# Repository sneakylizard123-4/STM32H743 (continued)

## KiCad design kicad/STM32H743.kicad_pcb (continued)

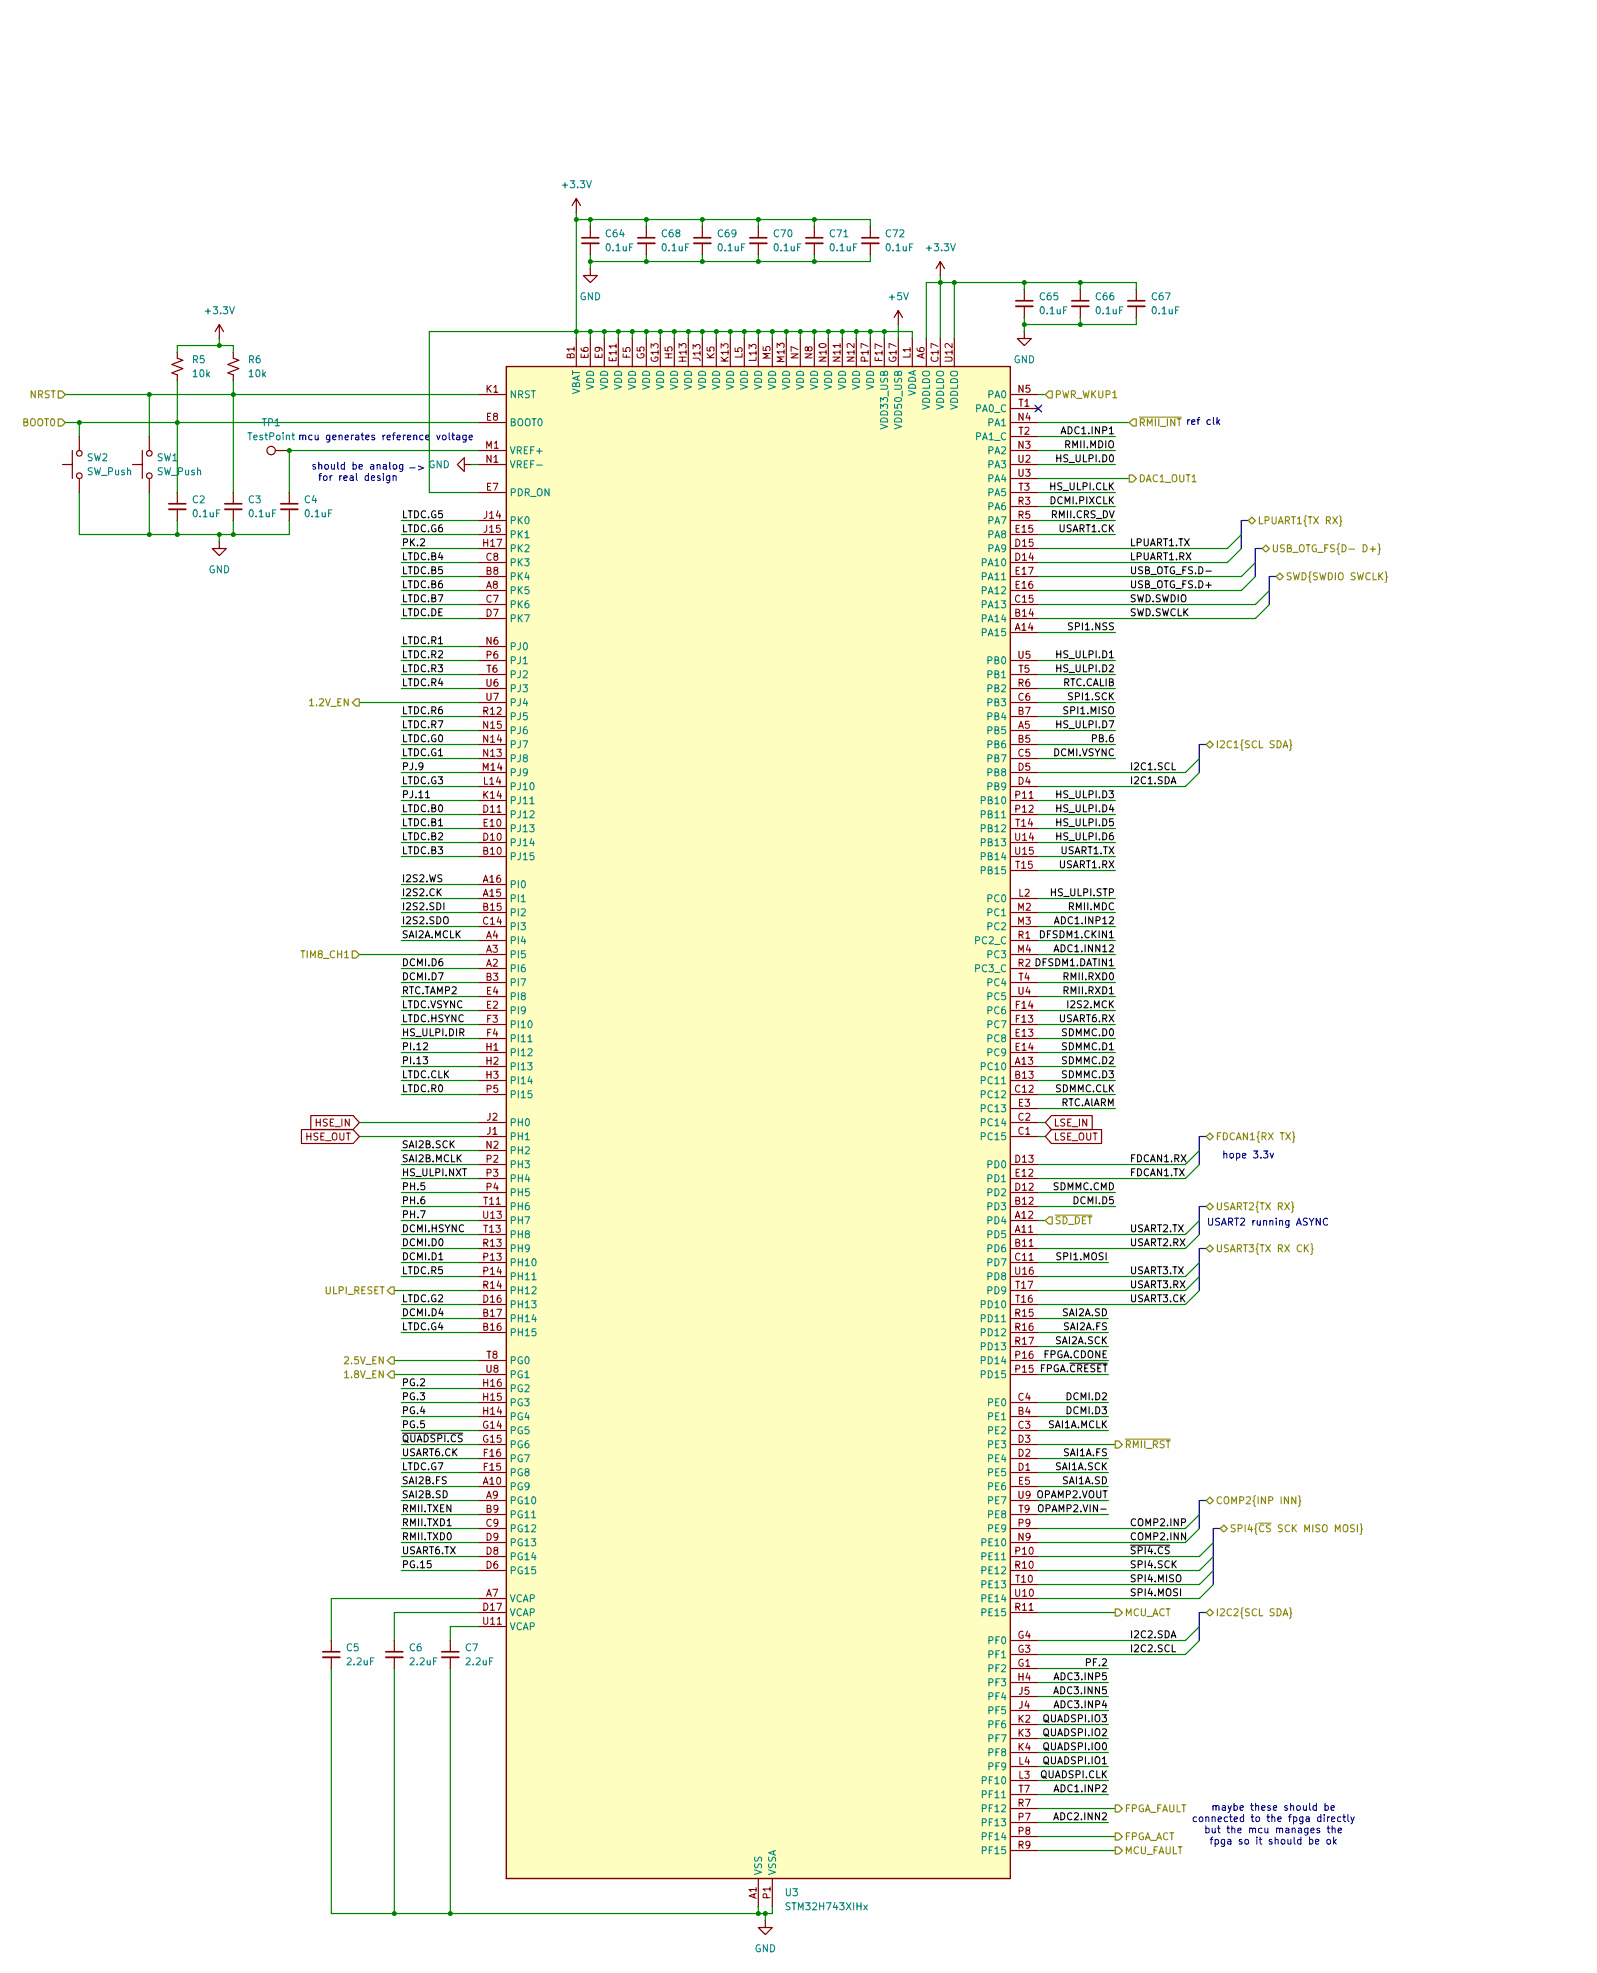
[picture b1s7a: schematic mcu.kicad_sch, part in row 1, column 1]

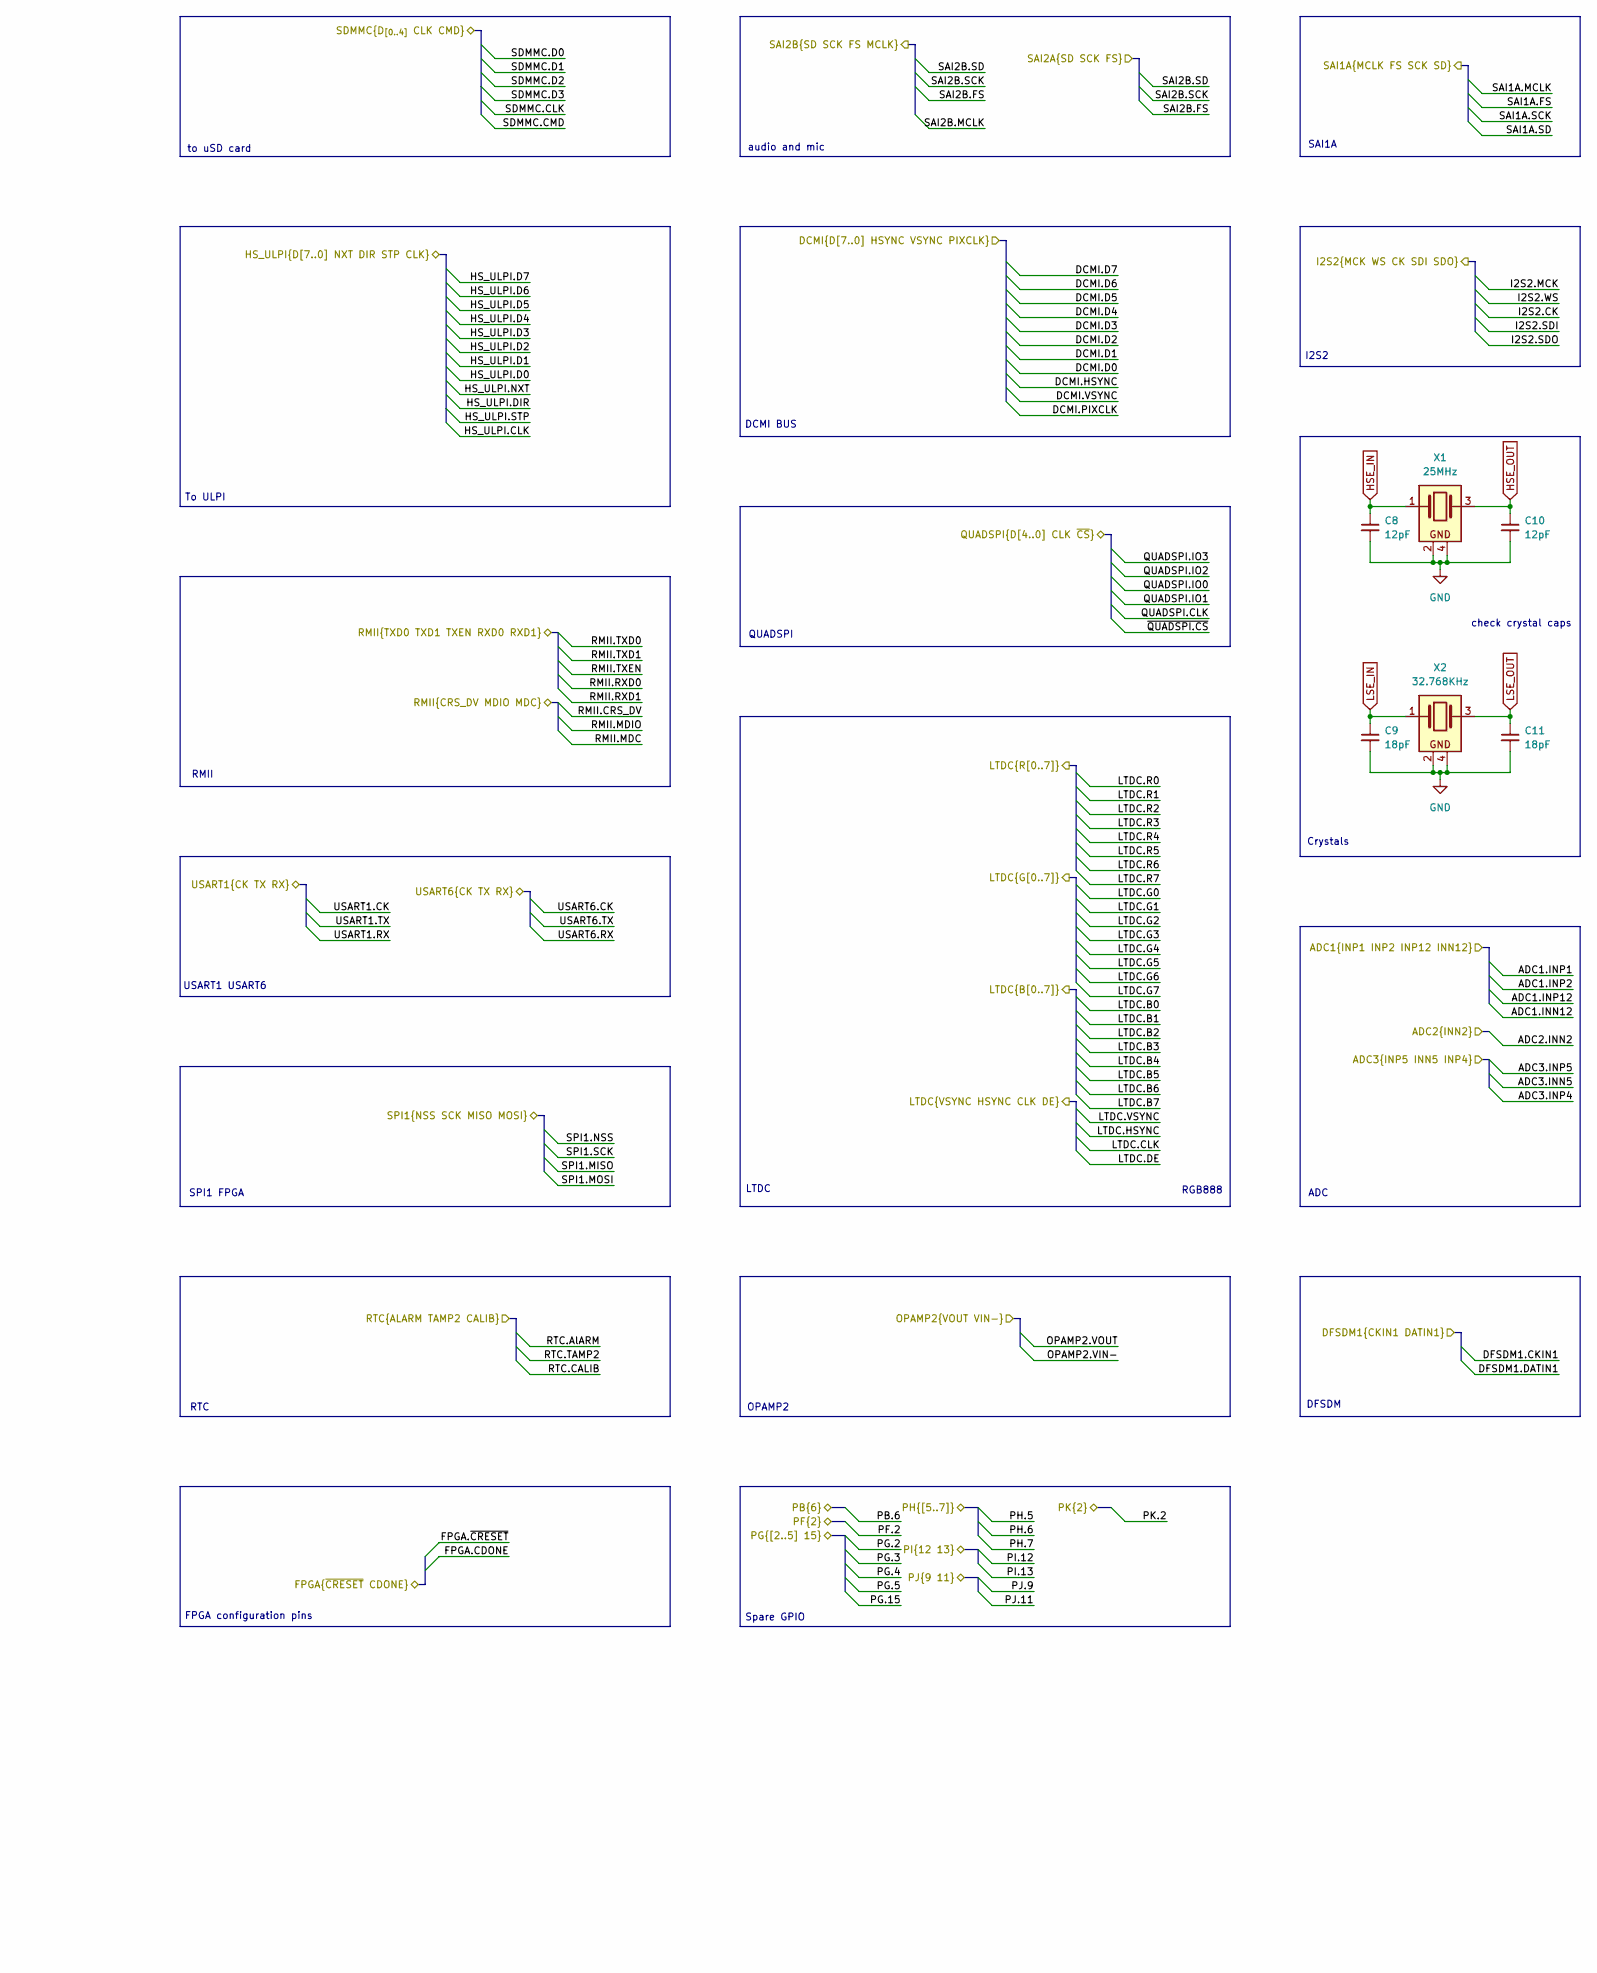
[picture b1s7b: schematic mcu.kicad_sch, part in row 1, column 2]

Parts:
C2, C3, C4, C64, C65, C66, C67, C68, C69, C70, C71, C72: 0.1uF; C_0603_1608Metric
C5, C6, C7: 2.2uF; C_0603_1608Metric
C8, C10: 12pF; C_0603_1608Metric
C9, C11: 18pF; C_0603_1608Metric
R5, R6: 10k; R_0603_1608Metric
SW1, SW2: SW_Push; Panasonic_EVQPUM_EVQPUD
TP1: TestPoint; TestPoint_Pad_D1.5mm
U3: STM32H743XIHx; TFBGA-265_14x14mm_Layout17x17_P0.8mm
X1: 25MHz; Crystal_SMD_3225-4Pin_3.2x2.5mm
X2: 32.768KHz; Crystal_SMD_3225-4Pin_3.2x2.5mm

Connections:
+3.3V: C64.1, C65.1, C66.1, C67.1, C68.1, C69.1, C70.1, C71.1, C72.1, R5.1, R6.1, U3.A6 (VDDLDO), U3.B1 (VBAT), U3.C17 (VDDLDO), U3.E6 (VDD), U3.E7 (PDR_ON), U3.E9 (VDD), U3.E11 (VDD), U3.F5 (VDD), U3.F17 (VDD33_USB), U3.G5 (VDD), U3.G13 (VDD), U3.H5 (VDD), U3.H13 (VDD), U3.J13 (VDD), U3.K5 (VDD), U3.K13 (VDD), U3.L1 (VDDA), U3.L5 (VDD), U3.L13 (VDD), U3.M5 (VDD), U3.M13 (VDD), U3.N7 (VDD), U3.N8 (VDD), U3.N10 (VDD), U3.N11 (VDD), U3.N12 (VDD), U3.P17 (VDD), U3.U12 (VDDLDO); also elsewhere on the board
+5V: U3.G17 (VDD50_USB); also elsewhere on the board
/Audio/DFSDM1.CKIN1: U3.R1 (PC2_C); also elsewhere on the board
/Audio/DFSDM1.DATIN1: U3.R2 (PC3_C); also elsewhere on the board
/Audio/SAI2A.FS: U3.R16 (PD12); also elsewhere on the board
/Audio/SAI2A.SCK: U3.R17 (PD13); also elsewhere on the board
/Audio/SAI2A.SD: U3.R15 (PD11); also elsewhere on the board
/Audio/SAI2B.FS: U3.A10 (PG9); also elsewhere on the board
/Audio/SAI2B.MCLK: U3.P2 (PH3); also elsewhere on the board
/Audio/SAI2B.SCK: U3.N2 (PH2); also elsewhere on the board
/Audio/SAI2B.SD: U3.A9 (PG10); also elsewhere on the board
/Clock/I2C1.SCL: U3.D5 (PB8); also elsewhere on the board
/Clock/I2C1.SDA: U3.D4 (PB9); also elsewhere on the board
/Connector/ADC1.INN12: U3.M4 (PC3)
/Connector/ADC1.INP1: U3.T2 (PA1_C)
/Connector/ADC1.INP2: U3.T7 (PF11)
/Connector/ADC1.INP12: U3.M3 (PC2)
/Connector/ADC2.INN2: U3.P7 (PF13)
/Connector/ADC3.INN5: U3.J5 (PF4)
/Connector/ADC3.INP4: U3.J4 (PF5)
/Connector/ADC3.INP5: U3.H4 (PF3)
/Connector/BOOT0: C2.1, R5.2, SW2.2, U3.E8 (BOOT0)
/Connector/COMP2.INN: U3.N9 (PE10)
/Connector/COMP2.INP: U3.P9 (PE9)
/Connector/DAC1_OUT1: U3.U3 (PA4)
/Connector/DCMI.D0: U3.R13 (PH9)
/Connector/DCMI.D1: U3.P13 (PH10)
/Connector/DCMI.D2: U3.C4 (PE0)
/Connector/DCMI.D3: U3.B4 (PE1)
/Connector/DCMI.D4: U3.B17 (PH14)
/Connector/DCMI.D5: U3.B12 (PD3)
/Connector/DCMI.D6: U3.A2 (PI6)
/Connector/DCMI.D7: U3.B3 (PI7)
/Connector/DCMI.HSYNC: U3.T13 (PH8)
/Connector/DCMI.PIXCLK: U3.R3 (PA6)
/Connector/DCMI.VSYNC: U3.C5 (PB7)
/Connector/FDCAN1.RX: U3.D13 (PD0)
/Connector/FDCAN1.TX: U3.E12 (PD1)
/Connector/I2C2.SCL: U3.G3 (PF1)
/Connector/I2C2.SDA: U3.G4 (PF0)
/Connector/I2S2.CK: U3.A15 (PI1)
/Connector/I2S2.MCK: U3.F14 (PC6)
/Connector/I2S2.SDI: U3.B15 (PI2)
/Connector/I2S2.SDO: U3.C14 (PI3)
/Connector/I2S2.WS: U3.A16 (PI0)
/Connector/LPUART1.RX: U3.D14 (PA10)
/Connector/LPUART1.TX: U3.D15 (PA9)
/Connector/NRST: C3.1, R6.2, SW1.2, U3.K1 (NRST); also elsewhere on the board
/Connector/OPAMP2.VIN-: U3.T9 (PE8)
/Connector/OPAMP2.VOUT: U3.U9 (PE7)
/Connector/PWR_WKUP1: U3.N5 (PA0)
/Connector/QUADSPI.CLK: U3.L3 (PF10)
/Connector/RTC.CALIB: U3.R6 (PB2)
/Connector/RTC.TAMP2: U3.E4 (PI8)
/Connector/SAI1A.FS: U3.D2 (PE4)
/Connector/SAI1A.MCLK: U3.C3 (PE2)
/Connector/SAI1A.SCK: U3.D1 (PE5)
/Connector/SAI1A.SD: U3.E5 (PE6)
/Connector/SPI4.MISO: U3.T10 (PE13)
/Connector/SPI4.MOSI: U3.U10 (PE14)
/Connector/SPI4.SCK: U3.R10 (PE12)
/Connector/TIM8_CH1: U3.A3 (PI5)
/Connector/USART1.CK: U3.E15 (PA8)
/Connector/USART1.RX: U3.T15 (PB15)
/Connector/USART1.TX: U3.U15 (PB14)
/Connector/USART2.RX: U3.B11 (PD6)
/Connector/USART2.TX: U3.A11 (PD5)
/Connector/USART3.CK: U3.T16 (PD10)
/Connector/USART3.RX: U3.T17 (PD9)
/Connector/USART3.TX: U3.U16 (PD8)
/Connector/USART6.CK: U3.F16 (PG7)
/Connector/USART6.RX: U3.F13 (PC7)
/Connector/USART6.TX: U3.D8 (PG14)
/Ethernet/RMII.CRS_DV: U3.R5 (PA7); also elsewhere on the board
/Ethernet/RMII.MDC: U3.M2 (PC1); also elsewhere on the board
/Ethernet/RMII.MDIO: U3.N3 (PA2); also elsewhere on the board
/Ethernet/RMII.RXD0: U3.T4 (PC4); also elsewhere on the board
/Ethernet/RMII.RXD1: U3.U4 (PC5); also elsewhere on the board
/Ethernet/RMII.TXD0: U3.D9 (PG13); also elsewhere on the board
/Ethernet/RMII.TXD1: U3.C9 (PG12); also elsewhere on the board
/Ethernet/RMII.TXEN: U3.B9 (PG11); also elsewhere on the board
/Ethernet/~RMII_INT: U3.N4 (PA1); also elsewhere on the board
/Ethernet/~RMII_RST: U3.D3 (PE3); also elsewhere on the board
/FPGA/FPGA.CDONE: U3.P16 (PD14); also elsewhere on the board
/FPGA/FPGA.~CRESET: U3.P15 (PD15); also elsewhere on the board
/FPGA/SPI1.MISO: U3.B7 (PB4); also elsewhere on the board
/FPGA/SPI1.MOSI: U3.C11 (PD7); also elsewhere on the board
/FPGA/SPI1.NSS: U3.A14 (PA15); also elsewhere on the board
/FPGA/SPI1.SCK: U3.C6 (PB3); also elsewhere on the board
/GPIO/PB.6: U3.B5 (PB6); also elsewhere on the board
/GPIO/PF.2: U3.G1 (PF2); also elsewhere on the board
/GPIO/PG.2: U3.H16 (PG2); also elsewhere on the board
/GPIO/PG.3: U3.H15 (PG3); also elsewhere on the board
/GPIO/PG.4: U3.H14 (PG4); also elsewhere on the board
/GPIO/PG.5: U3.G14 (PG5); also elsewhere on the board
/GPIO/PG.15: U3.D6 (PG15); also elsewhere on the board
/GPIO/PH.5: U3.P4 (PH5); also elsewhere on the board
/GPIO/PH.6: U3.T11 (PH6); also elsewhere on the board
/GPIO/PH.7: U3.U13 (PH7); also elsewhere on the board
/GPIO/PI.12: U3.H1 (PI12); also elsewhere on the board
/GPIO/PI.13: U3.H2 (PI13); also elsewhere on the board
/GPIO/PJ.9: U3.M14 (PJ9); also elsewhere on the board
/GPIO/PJ.11: U3.K14 (PJ11); also elsewhere on the board
/GPIO/PK.2: U3.H17 (PK2); also elsewhere on the board
/LEDs/FPGA_ACT: U3.P8 (PF14); also elsewhere on the board
/LEDs/FPGA_FAULT: U3.R7 (PF12); also elsewhere on the board
/LEDs/MCU_ACT: U3.R11 (PE15); also elsewhere on the board
/LEDs/MCU_FAULT: U3.R9 (PF15); also elsewhere on the board
/LTDC/LTDC.B0: U3.D11 (PJ12)
/LTDC/LTDC.B1: U3.E10 (PJ13)
/LTDC/LTDC.B2: U3.D10 (PJ14)
/LTDC/LTDC.B3: U3.B10 (PJ15)
/LTDC/LTDC.B4: U3.C8 (PK3)
/LTDC/LTDC.B5: U3.B8 (PK4)
/LTDC/LTDC.B6: U3.A8 (PK5)
/LTDC/LTDC.B7: U3.C7 (PK6)
/LTDC/LTDC.CLK: U3.H3 (PI14)
/LTDC/LTDC.DE: U3.D7 (PK7)
/LTDC/LTDC.G0: U3.N14 (PJ7)
/LTDC/LTDC.G1: U3.N13 (PJ8)
/LTDC/LTDC.G2: U3.D16 (PH13)
/LTDC/LTDC.G3: U3.L14 (PJ10)
/LTDC/LTDC.G4: U3.B16 (PH15)
/LTDC/LTDC.G5: U3.J14 (PK0)
/LTDC/LTDC.G6: U3.J15 (PK1)
/LTDC/LTDC.G7: U3.F15 (PG8)
/LTDC/LTDC.HSYNC: U3.F3 (PI10)
/LTDC/LTDC.R0: U3.P5 (PI15)
/LTDC/LTDC.R1: U3.N6 (PJ0)
/LTDC/LTDC.R2: U3.P6 (PJ1)
/LTDC/LTDC.R3: U3.T6 (PJ2)
/LTDC/LTDC.R4: U3.U6 (PJ3)
/LTDC/LTDC.R5: U3.P14 (PH11)
/LTDC/LTDC.R6: U3.R12 (PJ5)
/LTDC/LTDC.R7: U3.N15 (PJ6)
/LTDC/LTDC.VSYNC: U3.E2 (PI9)
/MCU/1.2V_EN: U3.U7 (PJ4); also elsewhere on the board
/MCU/1.8V_EN: U3.U8 (PG1); also elsewhere on the board
/MCU/2.5V_EN: U3.T8 (PG0); also elsewhere on the board
/MCU/HS_ULPI.CLK: U3.T3 (PA5); also elsewhere on the board
/MCU/HS_ULPI.D0: U3.U2 (PA3); also elsewhere on the board
/MCU/HS_ULPI.D1: U3.U5 (PB0); also elsewhere on the board
/MCU/HS_ULPI.D2: U3.T5 (PB1); also elsewhere on the board
/MCU/HS_ULPI.D3: U3.P11 (PB10); also elsewhere on the board
/MCU/HS_ULPI.D4: U3.P12 (PB11); also elsewhere on the board
/MCU/HS_ULPI.D5: U3.T14 (PB12); also elsewhere on the board
/MCU/HS_ULPI.D6: U3.U14 (PB13); also elsewhere on the board
/MCU/HS_ULPI.D7: U3.A5 (PB5); also elsewhere on the board
/MCU/HS_ULPI.DIR: U3.F4 (PI11); also elsewhere on the board
/MCU/HS_ULPI.NXT: U3.P3 (PH4); also elsewhere on the board
/MCU/HS_ULPI.STP: U3.L2 (PC0); also elsewhere on the board
/MCU/QUADSPI.IO0: U3.K4 (PF8)
/MCU/QUADSPI.IO1: U3.L4 (PF9)
/MCU/QUADSPI.IO2: U3.K3 (PF7)
/MCU/QUADSPI.IO3: U3.K2 (PF6)
/MCU/RTC.AlARM: U3.E3 (PC13)
/MCU/SAI2A.MCLK: U3.A4 (PI4)
/MCU/USB_OTG_FS.D+: U3.E16 (PA12); also elsewhere on the board
/MCU/USB_OTG_FS.D-: U3.E17 (PA11); also elsewhere on the board
/MCU/~QUADSPI.CS: U3.G15 (PG6)
/MCU/~SD_DET: U3.A12 (PD4); also elsewhere on the board
/MCU/~SPI4.CS: U3.P10 (PE11)
GND: C2.2, C3.2, C4.2, C5.2, C6.2, C7.2, C8.2, C9.2, C10.2, C11.2, C64.2, C65.2, C66.2, C67.2, C68.2, C69.2, C70.2, C71.2, C72.2, SW1.1, SW2.1, U3.A1 (VSS), U3.A17 (VSS), U3.B2 (VSS), U3.B6 (VSS), U3.C10 (VSS), U3.C13 (VSS), U3.C16 (VSS), U3.F1 (VSS), U3.F2 (VSS), U3.G2 (VSS), U3.G7 (VSS), U3.G8 (VSS), U3.G9 (VSS), U3.G10 (VSS), U3.G11 (VSS), U3.G16 (VSS), U3.H7 (VSS), U3.H8 (VSS), U3.H9 (VSS), U3.H10 (VSS), U3.H11 (VSS), U3.J3 (VSS), U3.J7 (VSS), U3.J8 (VSS), U3.J9 (VSS), U3.J10 (VSS), U3.J11 (VSS), U3.J16 (VSS), U3.J17 (VSS), U3.K7 (VSS), U3.K8 (VSS), U3.K9 (VSS), U3.K10 (VSS), U3.K11 (VSS), U3.K15 (VSS), U3.L7 (VSS), U3.L8 (VSS), U3.L9 (VSS), U3.L10 (VSS), U3.L11 (VSS), U3.L15 (VSS), U3.M15 (VSS), U3.N1 (VREF-), U3.N16 (VSS), U3.P1 (VSSA), U3.R4 (VSS), U3.R8 (VSS), U3.T12 (VSS), U3.U1 (VSS), U3.U17 (VSS), X1.2, X1.4, X2.2, X2.4; also elsewhere on the board
HSE_IN: C8.1, U3.J2 (PH0), X1.1
HSE_OUT: C10.1, U3.J1 (PH1), X1.3
LSE_IN: C9.1, U3.C2 (PC14), X2.1
LSE_OUT: C11.1, U3.C1 (PC15), X2.3
unnamed: C5.1, U3.A7 (VCAP)
unnamed: C6.1, U3.D17 (VCAP)
unnamed: C7.1, U3.U11 (VCAP)
unnamed: C4.1, TP1.1 (1_1), U3.M1 (VREF+)
SD_CLK: U3.C12; also elsewhere on the board
SD_CMD: U3.D12 (PD2); also elsewhere on the board
SD_DAT0: U3.E13 (PC8); also elsewhere on the board
SD_DAT1: U3.E14 (PC9); also elsewhere on the board
SD_DAT2: U3.A13 (PC10); also elsewhere on the board
SD_DAT3: U3.B13 (PC11); also elsewhere on the board
SWCLK: U3.B14 (PA14); also elsewhere on the board
SWDIO: U3.C15 (PA13); also elsewhere on the board
~ULPI_RESET: U3.R14 (PH12); also elsewhere on the board

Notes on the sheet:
RGB888
SAI1A
USART2 running ASYNC
mcu generates reference voltage
Spare GPIO
OPAMP2
I2S2
To ULPI
audio and mic
ADC
DCMI BUS
maybe these should be connected to the fpga directly but the mcu manages the fpga so it should be ok
check crystal caps
RMII
SPI1 FPGA
LTDC
to uSD card
FPGA configuration pins
USART1 USART6
QUADSPI
RTC
should be analog for real design
hope 3.3v
ref clk
DFSDM
Crystals

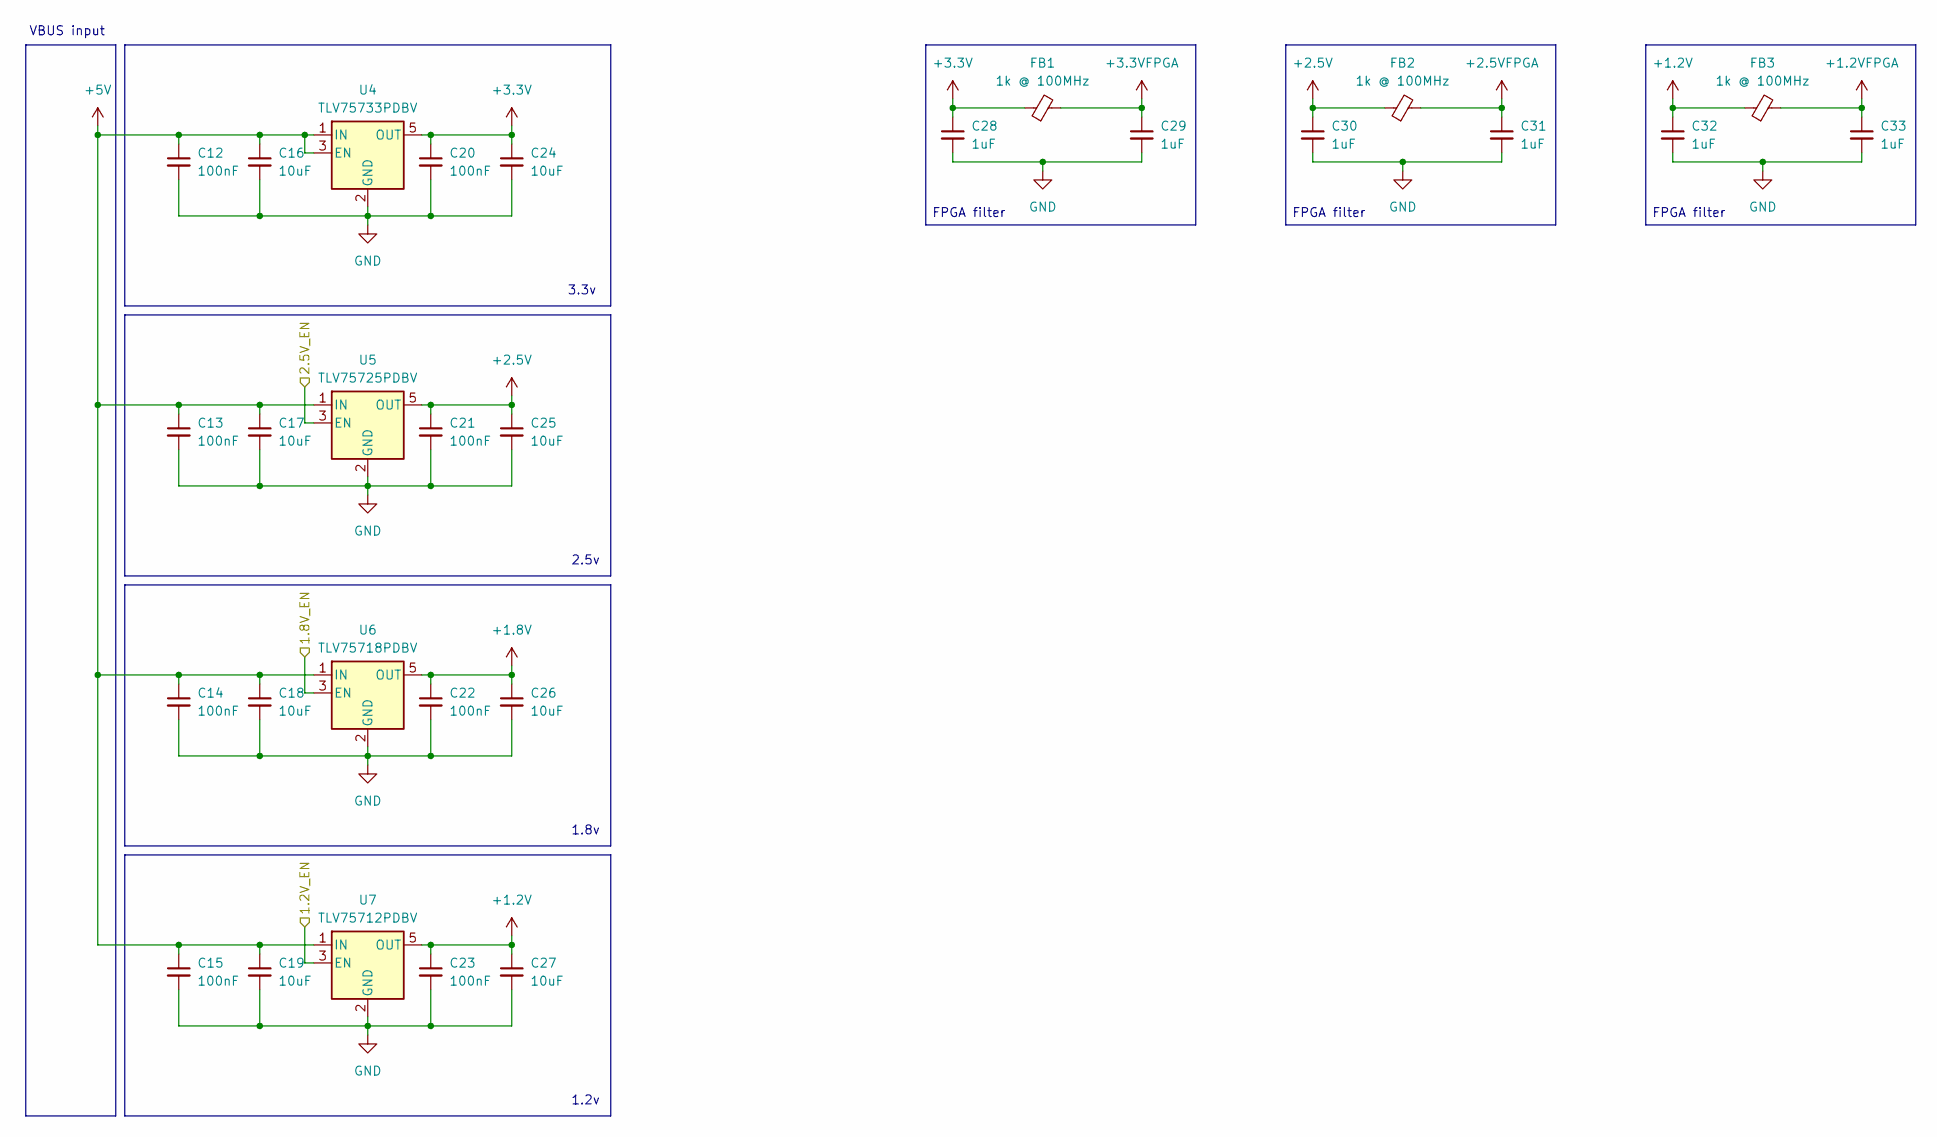
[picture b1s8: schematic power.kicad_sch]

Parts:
C12, C13, C14, C15, C20, C21, C22, C23: 100nF; C_0603_1608Metric
C16, C17, C18, C19, C24, C25, C26, C27: 10uF; C_0603_1608Metric
C28, C29, C30, C31, C32, C33: 1uF; C_0603_1608Metric
FB1, FB2, FB3: 1k @ 100MHz; Ferrite_0603_1608Metric
U4: TLV75733PDBV; SOT-23-5
U5: TLV75725PDBV; SOT-23-5
U6: TLV75718PDBV; SOT-23-5
U7: TLV75712PDBV; SOT-23-5

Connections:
+1.2V: C23.1, C27.1, C32.1, FB3.1, U7.5 (OUT); also elsewhere on the board
+1.2VFPGA: C33.1, FB3.2; also elsewhere on the board
+1.8V: C22.1, C26.1, U6.5 (OUT); also elsewhere on the board
+2.5V: C21.1, C25.1, C30.1, FB2.1, U5.5 (OUT); also elsewhere on the board
+2.5VFPGA: C31.1, FB2.2; also elsewhere on the board
+3.3V: C20.1, C24.1, C28.1, FB1.1, U4.5 (OUT); also elsewhere on the board
+3.3VFPGA: C29.1, FB1.2; also elsewhere on the board
+5V: C12.1, C13.1, C14.1, C15.1, C16.1, C17.1, C18.1, C19.1, U4.1 (IN), U4.3 (EN), U5.1 (IN), U6.1 (IN), U7.1 (IN); also elsewhere on the board
/MCU/1.2V_EN: U7.3 (EN); also elsewhere on the board
/MCU/1.8V_EN: U6.3 (EN); also elsewhere on the board
/MCU/2.5V_EN: U5.3 (EN); also elsewhere on the board
GND: C12.2, C13.2, C14.2, C15.2, C16.2, C17.2, C18.2, C19.2, C20.2, C21.2, C22.2, C23.2, C24.2, C25.2, C26.2, C27.2, C28.2, C29.2, C30.2, C31.2, C32.2, C33.2, U4.2 (GND), U5.2 (GND), U6.2 (GND), U7.2 (GND); also elsewhere on the board

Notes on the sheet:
1.8v
VBUS input
3.3v
FPGA filter
2.5v
1.2v

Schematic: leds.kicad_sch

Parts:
D3, D4, D5, D6: GREEN; LED_0603_1608Metric
D7, D9: YELLOW; LED_0603_1608Metric
D8, D10: RED; LED_0603_1608Metric
RN1, RN2: 1k; R_Array_Concave_4x0603

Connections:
+1.2V: RN1.1 (R1.1); also elsewhere on the board
+1.8V: RN1.2 (R2.1); also elsewhere on the board
+2.5V: RN1.3 (R3.1); also elsewhere on the board
+3.3V: RN1.4 (R4.1); also elsewhere on the board
/LEDs/FPGA_ACT: RN2.2 (R2.1); also elsewhere on the board
/LEDs/FPGA_FAULT: RN2.1 (R1.1); also elsewhere on the board
/LEDs/MCU_ACT: RN2.4 (R4.1); also elsewhere on the board
/LEDs/MCU_FAULT: RN2.3 (R3.1); also elsewhere on the board
GND: D3.1 (K), D4.1 (K), D5.1 (K), D6.1 (K), D7.1 (K), D8.1 (K), D9.1 (K), D10.1 (K); also elsewhere on the board
unnamed: D3.2 (A), RN1.5 (R4.2)
unnamed: D4.2 (A), RN1.6 (R3.2)
unnamed: D5.2 (A), RN1.7 (R2.2)
unnamed: D6.2 (A), RN1.8 (R1.2)
unnamed: D7.2 (A), RN2.5 (R4.2)
unnamed: D8.2 (A), RN2.6 (R3.2)
unnamed: D9.2 (A), RN2.7 (R2.2)
unnamed: D10.2 (A), RN2.8 (R1.2)

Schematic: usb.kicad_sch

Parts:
C1: 120uF; C_0603_1608Metric
D1, D2: SMF12A; D_SMF
J1: USB_A; USB_A_Connfly_DS1095
J2: USB_C_Receptacle_USB2.0_16P; USB_C_Receptacle_HRO_TYPE-C-31-M-12
R1, R2: 22; R_0603_1608Metric
R3, R4: 5.1k; R_0603_1608Metric
U1, U2: USBLC6-2SC6; SOT-23-6

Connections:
+5V: D2.1 (A1), J2.A4 (VBUS), J2.A9 (VBUS), J2.B4 (VBUS), J2.B9 (VBUS), U2.5 (VBUS); also elsewhere on the board
/MCU/USB_OTG_FS.D+: R2.2; also elsewhere on the board
/MCU/USB_OTG_FS.D-: R1.2; also elsewhere on the board
/ULPI/USBA.D+: U1.4 (I/O2); also elsewhere on the board
/ULPI/USBA.D-: U1.6 (I/O1); also elsewhere on the board
/ULPI/USBA.VBUS: C1.1, D1.1 (A1), J1.1 (VBUS), U1.5 (VBUS); also elsewhere on the board
GND: C1.2, D1.2 (A2), D2.2 (A2), J1.4 (GND), J1.SH (Shield), J2.A1 (GND), J2.A12 (GND), J2.B1 (GND), J2.B12 (GND), J2.SH (SHIELD), R3.2, R4.2, U1.2 (GND), U2.2 (GND); also elsewhere on the board
unnamed: J1.3 (D+), U1.1 (I/O1)
unnamed: J1.2 (D-), U1.3 (I/O2)
unnamed: J2.A5 (CC1), R4.1
unnamed: J2.B5 (CC2), R3.1
unnamed: J2.A6 (D+), J2.B6 (D+), U2.3 (I/O2)
unnamed: J2.A7 (D-), J2.B7 (D-), U2.1 (I/O1)
unnamed: R1.1, U2.6 (I/O1)
unnamed: R2.1, U2.4 (I/O2)

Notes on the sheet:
anti zap
USB port
12v tvs
might run shield though capacitor later
USB Host
ringing prevention

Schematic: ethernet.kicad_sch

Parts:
C34: 1uF; C_0603_1608Metric
C35: 470pF; C_0603_1608Metric
C36: 22nF 50v; C_0603_1608Metric
C92, C93, C94, C95, C96: 0.1uF; C_0603_1608Metric
J3: RJ45_Halo_HFJ11-x2450E-LxxRL; RJ45_HALO_HFJ11-x2450E-LxxRL_Horizontal
R7, R8: 10k; R_0603_1608Metric
R9: 12.1k 1%; R_0603_1608Metric
R10, R11: 330; R_0603_1608Metric
U8: LAN8742A; VQFN-24-1EP_4x4mm_P0.5mm_EP2.5x2.5mm_ThermalVias

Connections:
+3.3V: C92.1, C93.1, C94.1, C95.1, C96.1, J3.9, J3.11, R7.1, R8.1, U8.1 (VDD2A), U8.9 (VDDIO), U8.19 (VDD1A); also elsewhere on the board
/Clock/ETH_CLK: U8.5 (XTAL1/CLKIN); also elsewhere on the board
/Ethernet/RD+: J3.3 (RD+), U8.23 (RXP)
/Ethernet/RD-: J3.6 (RD-), U8.22 (RXN)
/Ethernet/RMII.CRS_DV: U8.11 (CRS_DV/MODE2); also elsewhere on the board
/Ethernet/RMII.MDC: U8.13 (MDC); also elsewhere on the board
/Ethernet/RMII.MDIO: U8.12 (MDIO); also elsewhere on the board
/Ethernet/RMII.RXD0: U8.8 (RXD0/MODE0); also elsewhere on the board
/Ethernet/RMII.RXD1: U8.7 (RXD1/MODE1); also elsewhere on the board
/Ethernet/RMII.TXD0: U8.17 (TXD0); also elsewhere on the board
/Ethernet/RMII.TXD1: U8.18 (TXD1); also elsewhere on the board
/Ethernet/RMII.TXEN: U8.16 (TXEN); also elsewhere on the board
/Ethernet/TD+: J3.1 (TD+), U8.21 (TXP)
/Ethernet/TD-: J3.2 (TD-), U8.20 (TXN)
/Ethernet/~RMII_INT: R7.2, U8.14 (~INT/REFCLKO); also elsewhere on the board
/Ethernet/~RMII_RST: R8.2, U8.15 (~RST); also elsewhere on the board
ACTLED: R10.1, U8.3 (LED1/REGOFF)
GND: C34.2, C35.2, C36.2, C92.2, C93.2, C94.2, C95.2, C96.2, J3.8, J3.SH, R9.2, U8.25 (VSS); also elsewhere on the board
LINKLED: R11.1, U8.2 (LED2/~INTSEL)
unnamed: J3.10, R10.2
unnamed: J3.12, R11.2
unnamed: C36.1, J3.4 (TCT), J3.5 (RCT)
unnamed: R9.1, U8.24 (RBIAS)
unnamed: C34.1, C35.1, U8.6 (VDDCR)

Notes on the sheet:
check if this is correct
check this pin out
REFCLK

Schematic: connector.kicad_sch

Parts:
J6: Conn_02x05_Counter_Clockwise; PinSocket_2x05_P2.54mm_Vertical
J9: Conn_02x05_Odd_Even; PinHeader_2x05_P2.54mm_Vertical

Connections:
+1.2V: J6.5; also elsewhere on the board
+1.8V: J6.4; also elsewhere on the board
+2.5V: J6.3; also elsewhere on the board
+3.3V: J6.2, J9.7, J9.8; also elsewhere on the board
+5V: J6.1, J9.9, J9.10; also elsewhere on the board
/Connector/NRST: J9.1; also elsewhere on the board
GND: J6.6, J6.7, J6.8, J6.9, J6.10, J9.3, J9.4; also elsewhere on the board
SWCLK: J9.6; also elsewhere on the board
SWDIO: J9.2; also elsewhere on the board

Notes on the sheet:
camera
serial
NO CONNECTORS FOR V1!!
Analog
spi
timer
Power connector
SWD
i2c bus
audio
xternal mem
power
can bus
boot
timekeeping

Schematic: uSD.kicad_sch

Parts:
C37: 0.1uF; C_0603_1608Metric
J4: Micro_SD_Card_Det2; microSD_HC_Hirose_DM3D-SF
R12: 10k; R_0603_1608Metric

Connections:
+3.3V: C37.1, J4.4 (VDD), R12.1; also elsewhere on the board
/MCU/~SD_DET: J4.10 (DET_A), R12.2; also elsewhere on the board
GND: C37.2, J4.6 (VSS), J4.9 (DET_B), J4.SH (SHIELD); also elsewhere on the board
SD_CLK: J4.5 (CLK); also elsewhere on the board
SD_CMD: J4.3 (CMD); also elsewhere on the board
SD_DAT0: J4.7 (DAT0); also elsewhere on the board
SD_DAT1: J4.8 (DAT1); also elsewhere on the board
SD_DAT2: J4.1 (DAT2); also elsewhere on the board
SD_DAT3: J4.2 (DAT3/CD); also elsewhere on the board

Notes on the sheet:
Micro SD Slot
Bus connection

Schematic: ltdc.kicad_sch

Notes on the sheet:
Bus connection
